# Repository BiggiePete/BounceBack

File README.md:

# BounceBack
8S BMS board for electric skateboard and related applications

Vitrual bom:
https://biggiepete.github.io/BounceBack/

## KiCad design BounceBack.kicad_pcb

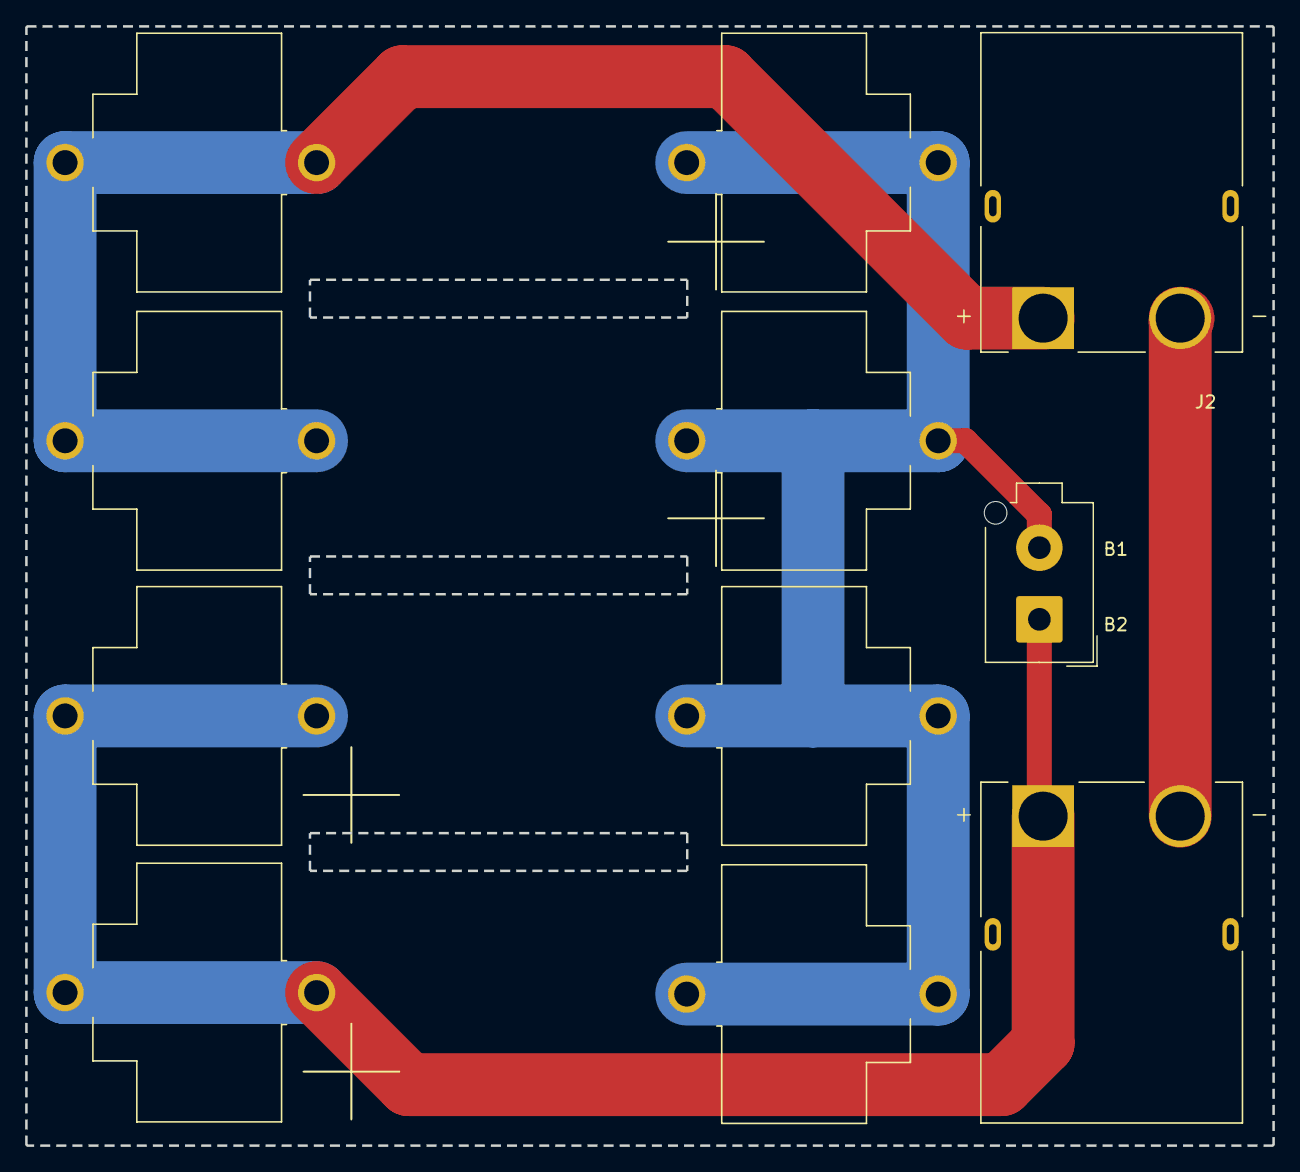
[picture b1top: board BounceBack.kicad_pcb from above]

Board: 2 copper layers, 99.2 x 89.0 mm, 11 parts (0 on the bottom side), 4 nets.

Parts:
BT33, BT34, BT35, BT36, BT37, BT38, BT39, BT40: 246; BAT_246
J1: XT90PW-M; AMASS_XT90PW-M
J2: XT90PW-F; AMASS_XT90PW-F
J3: Conn_01x02_Socket; Molex_Mega-Fit_76829-0102_2x01_P5.70mm_Vertical

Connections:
/Battery1/BAT+: BT33.A, BT34.A, BT39.A, BT40.A, J3.2
/Next_Cell: BT37.A, BT38.A, J1.P (POS), J3.1
/Prev_Cell: BT35.A, BT36.A, J2.P (POS)
unnamed: J1.N (NEG), J2.N (NEG)

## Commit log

2024-06-16 begin project
2024-06-17 fix footprints and layout board
2024-06-18 finish battery terminal placement
2024-06-22 adds connectors and bom
2024-06-22 add screenshot
